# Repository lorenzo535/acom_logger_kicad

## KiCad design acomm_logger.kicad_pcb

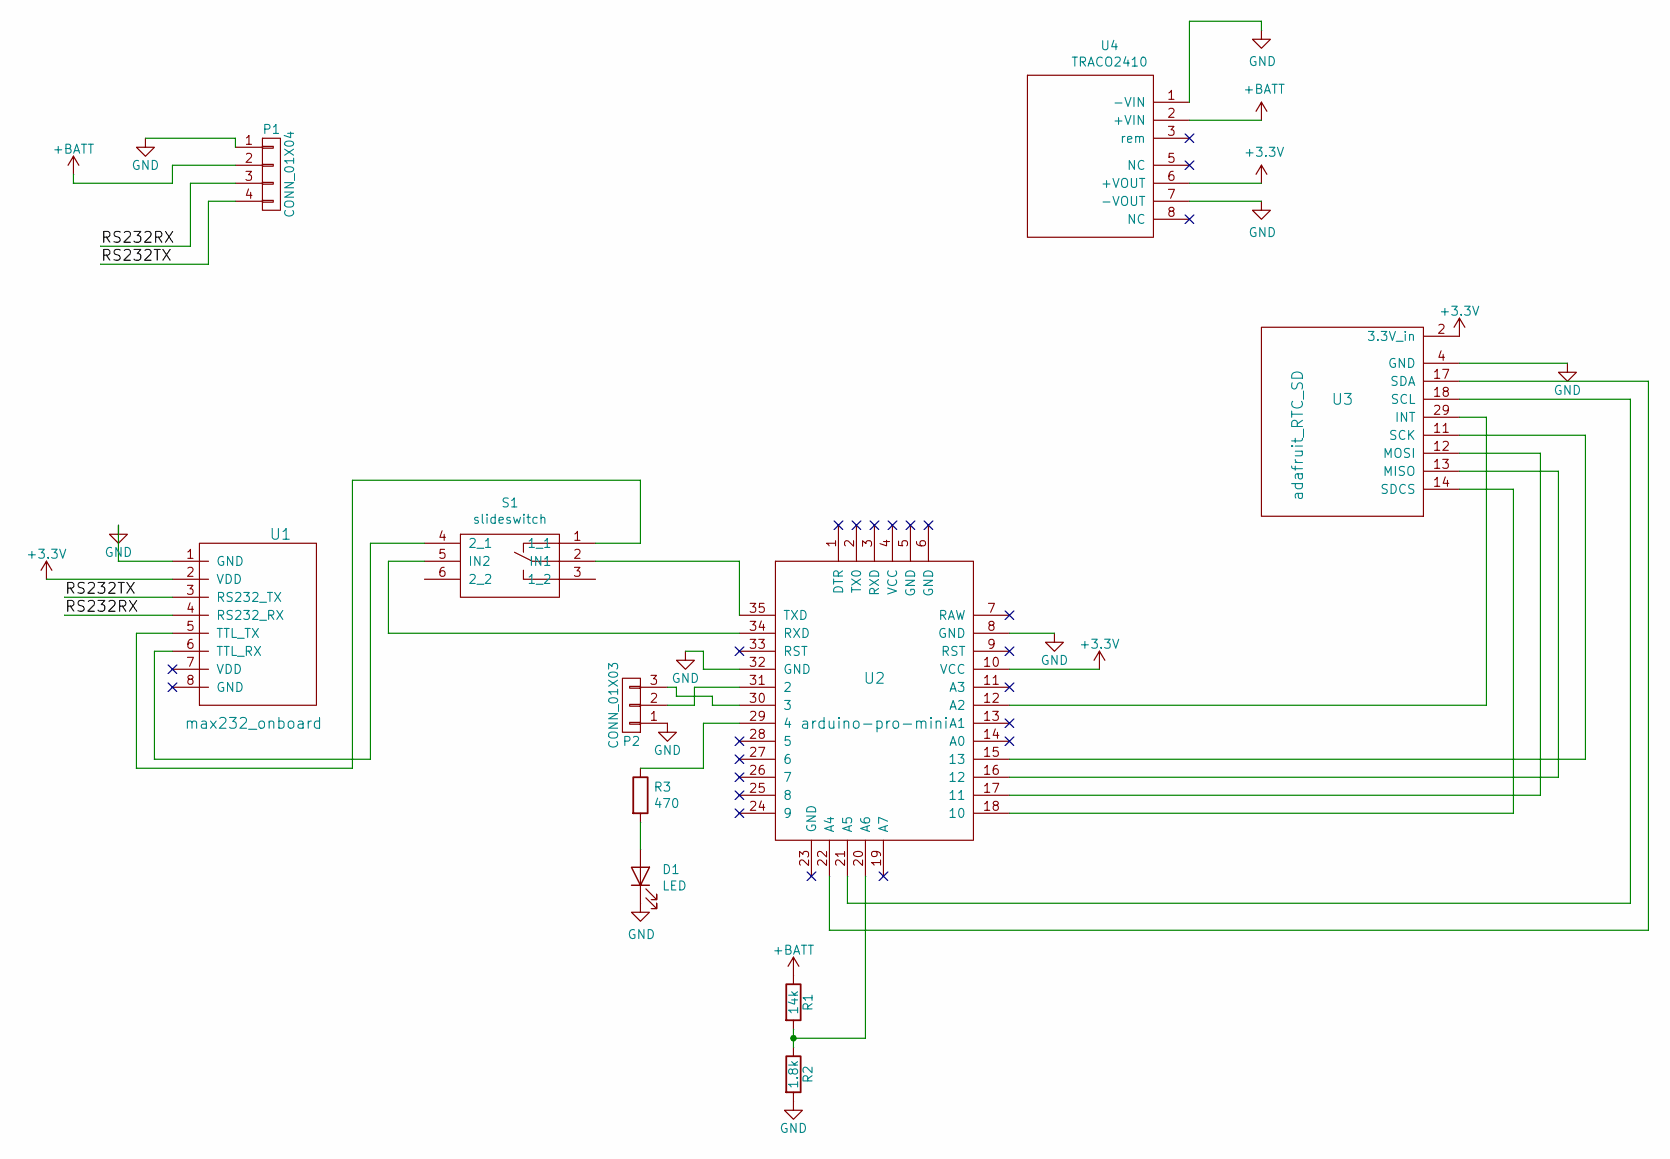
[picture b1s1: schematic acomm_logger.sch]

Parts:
D1: LED; LED_D4.0mm
P1: CONN_01X04; bornier_3.5_4
P2: CONN_01X03; PinHeader_1x03_P2.54mm_Vertical
R1: 14k; R_Axial_DIN0207_L6.3mm_D2.5mm_P7.62mm_Horizontal
R2: 1.8k; R_Axial_DIN0207_L6.3mm_D2.5mm_P7.62mm_Horizontal
R3: 470; R_Axial_DIN0207_L6.3mm_D2.5mm_P7.62mm_Horizontal
S1: slideswitch; slide_sxitch_TE_ASE2204
U1: max232_onboard; rs232_TTL_onboard
U2: arduino-pro-mini; ArduinoProMini
U3: adafruit_RTC_SD; AdafruitRTC_SD
U4: TRACO2410; Converter_DCDC_TRACO_TMR-xxxx_THT

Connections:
+3V3: U1.2 (VDD), U2.10 (VCC), U3.2 (3.3V_in), U4.6 (+VOUT)
+BATT: P1.2, R1.1, U4.2 (+VIN)
/RS232RX: P1.3, U1.4 (RS232_RX)
/RS232TX: P1.4, U1.3 (RS232_TX)
GND: D1.1 (K), P1.1, P2.1, R2.2, U1.1 (GND), U2.8 (GND), U2.32 (GND), U3.4 (GND), U4.1 (-VIN), U4.7 (-VOUT)
unnamed: D1.2 (A), R3.2
unnamed: P2.2, U2.31 (2)
unnamed: P2.3, U2.30 (3)
unnamed: R1.2, R2.1, U2.20 (A6)
unnamed: R3.1, U2.29 (4)
unnamed: S1.1 (1_1), U1.5 (TTL_TX)
unnamed: S1.2 (IN1), U2.35 (TXD)
unnamed: S1.4 (2_1), U1.6 (TTL_RX)
unnamed: S1.5 (IN2), U2.34 (RXD)
unnamed: U2.12 (A2), U3.29 (INT)
unnamed: U2.15 (13), U3.11 (SCK)
unnamed: U2.16 (12), U3.13 (MISO)
unnamed: U2.17 (11), U3.12 (MOSI)
unnamed: U2.18 (10), U3.14 (SDCS)
unnamed: U2.21 (A5), U3.18 (SCL)
unnamed: U2.22 (A4), U3.17 (SDA)

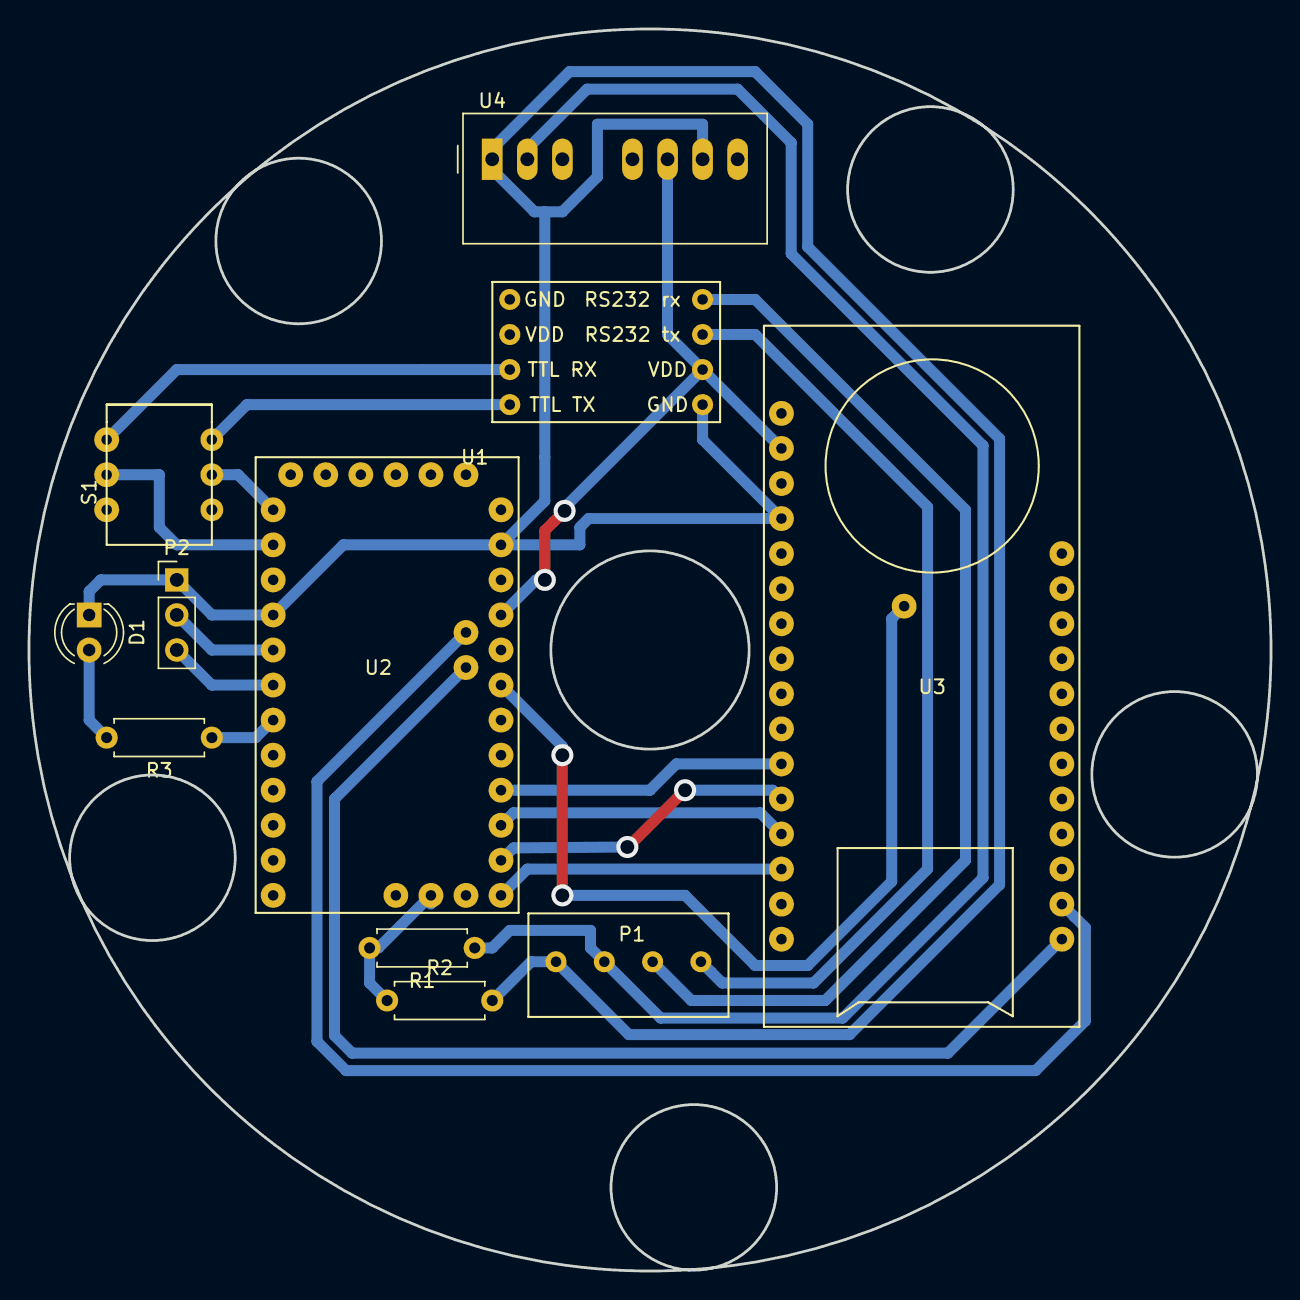
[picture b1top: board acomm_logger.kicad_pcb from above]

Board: 2 copper layers, 90.0 x 90.0 mm, 11 parts (0 on the bottom side), 21 nets.

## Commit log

2019-07-12 actual card used in trials
